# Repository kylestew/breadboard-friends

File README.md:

breadboard-friends
==================

https://mutable-instruments.net/archive/bbf/

A collection of cute breakout boards riding solderless breadboards, mostly for analog audio works

These PCB layouts and schematics are released under a Creative Commons cc-by-sa
3.0 license.

## On Oshpark

[Pots](https://oshpark.com/shared_projects/UcXFKgxV)
[Jacks](https://oshpark.com/shared_projects/G3ySjTBK)

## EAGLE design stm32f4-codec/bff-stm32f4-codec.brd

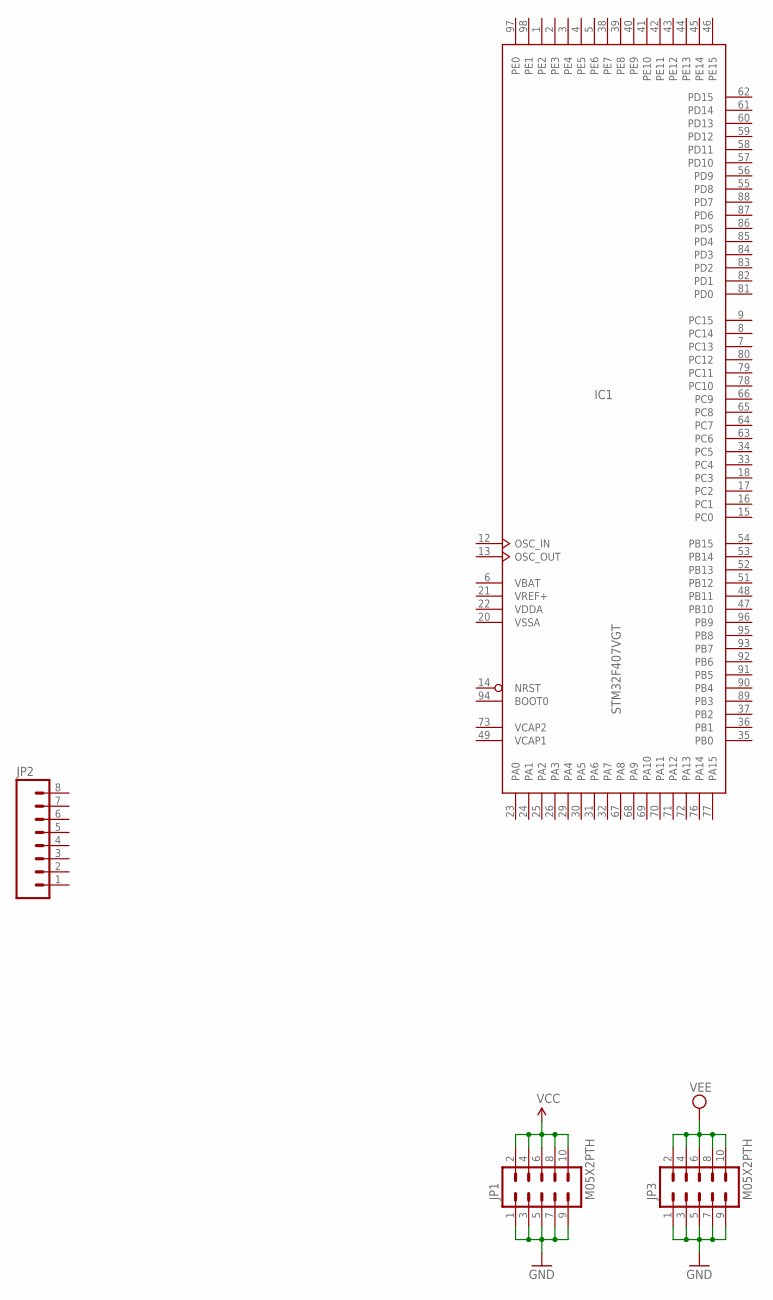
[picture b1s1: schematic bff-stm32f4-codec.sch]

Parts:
IC1: STM32F407VGT; LQFP100
JP1, JP3: M05X2PTH; AVR_ICSP
JP2: M08; 1X08

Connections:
GND: JP1.1, JP1.3, JP1.5, JP1.7, JP1.9, JP3.1, JP3.3, JP3.5, JP3.7, JP3.9
VBAT: IC1.6 (VBAT)
VCAP1: IC1.49 (VCAP1)
VCAP2: IC1.73 (VCAP2)
VCC: JP1.2, JP1.4, JP1.6, JP1.8, JP1.10
VDD: IC1.11 (VDD), IC1.19 (VDD), IC1.28 (VDD), IC1.50 (VDD), IC1.75 (VDD), IC1.100 (VDD)
VDDA: IC1.22 (VDDA)
VEE: JP3.2, JP3.4, JP3.6, JP3.8, JP3.10
VREF+: IC1.21 (VREF+)
VSS: IC1.10 (VSS), IC1.27 (VSS), IC1.74 (VSS), IC1.99 (VSS)
VSSA: IC1.20 (VSSA)

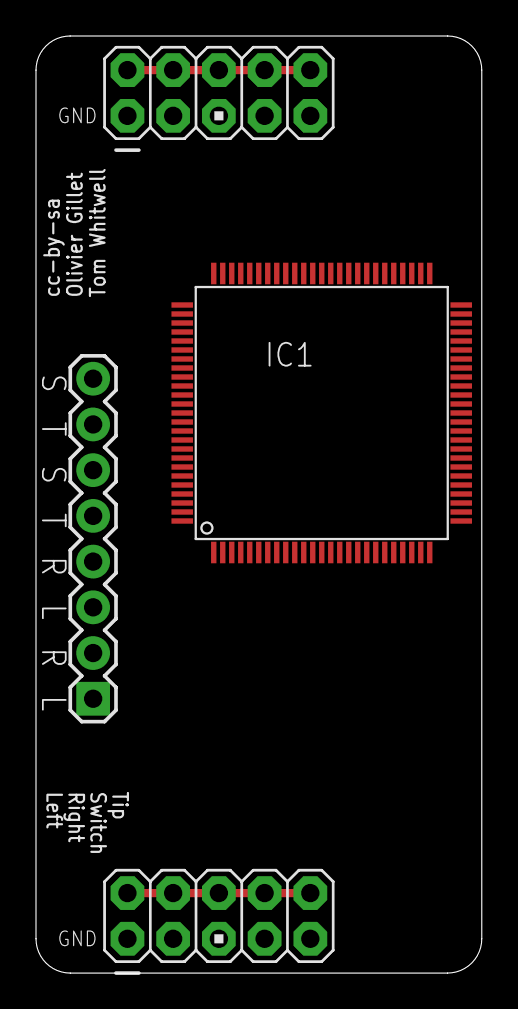
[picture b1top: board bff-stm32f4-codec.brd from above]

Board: 2 copper layers, 24.8 x 52.1 mm, 4 parts (0 on the bottom side), 5 nets.

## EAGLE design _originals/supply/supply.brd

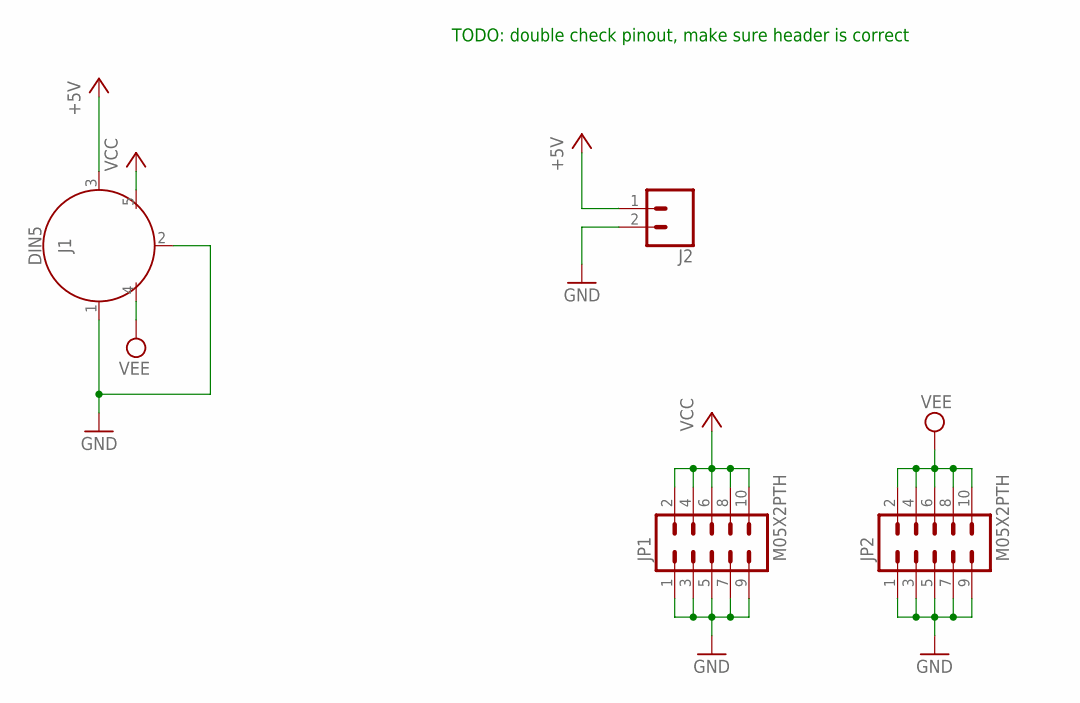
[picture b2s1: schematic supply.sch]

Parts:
J1: DIN5; DIN5-RA-PTH
J2: CONN_02; 1X02
JP1, JP2: M05X2PTH; AVR_ICSP

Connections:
+5V: J1.3, J2.1
GND: J1.1, J1.2, J2.2, JP1.1, JP1.3, JP1.5, JP1.7, JP1.9, JP2.1, JP2.3, JP2.5, JP2.7, JP2.9
VCC: J1.5, JP1.2, JP1.4, JP1.6, JP1.8, JP1.10
VEE: J1.4, JP2.2, JP2.4, JP2.6, JP2.8, JP2.10

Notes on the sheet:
TODO: double check pinout, make sure header is correct

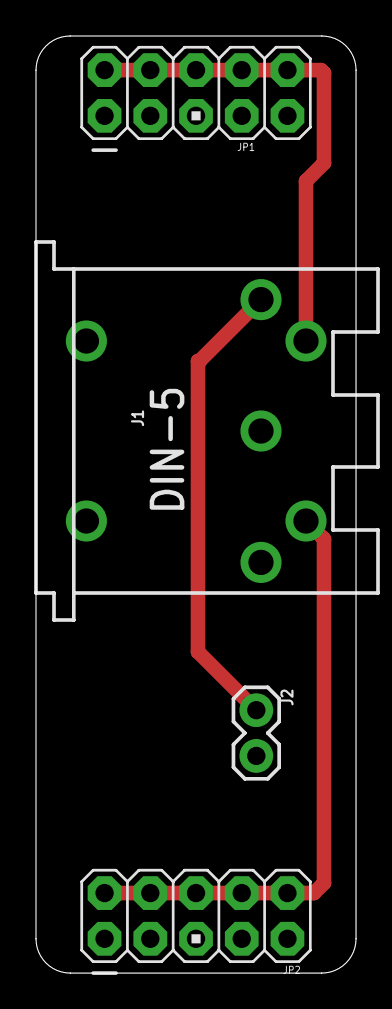
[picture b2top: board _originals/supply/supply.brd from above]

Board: 2 copper layers, 17.8 x 52.1 mm, 4 parts (0 on the bottom side), 4 nets.

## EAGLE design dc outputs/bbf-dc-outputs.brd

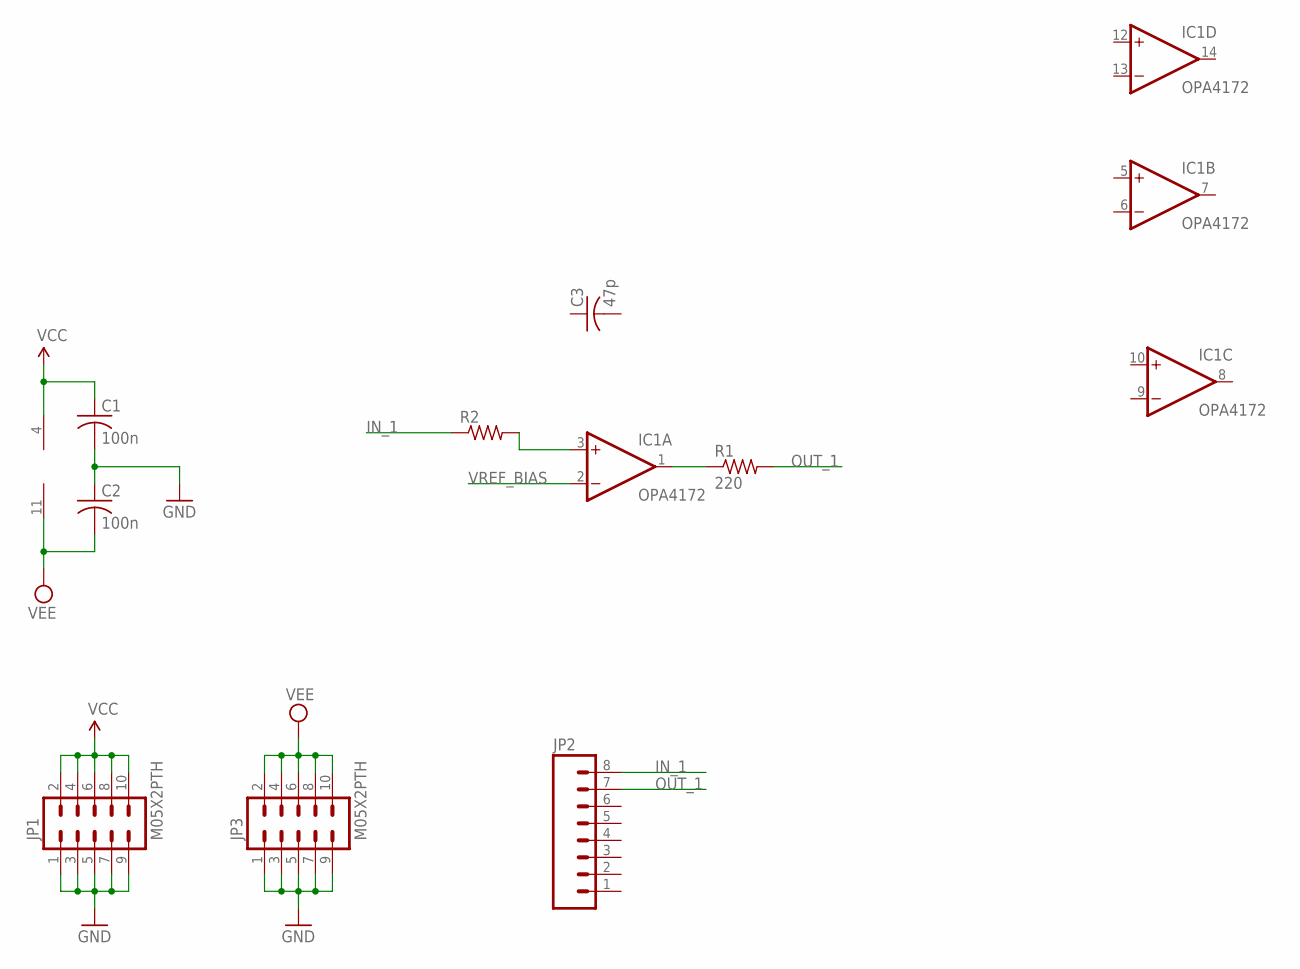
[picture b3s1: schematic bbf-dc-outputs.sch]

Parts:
C1, C2: 100n; C0805
C3: 47p; C0805
IC1: OPA4172; SO14
JP1, JP3: M05X2PTH; AVR_ICSP
JP2: M08; 1X08
R1: 220; R0805
R2: R-US_R0805; R0805

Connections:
GND: C1.2, C2.1, JP1.1, JP1.3, JP1.5, JP1.7, JP1.9, JP3.1, JP3.3, JP3.5, JP3.7, JP3.9
IN_1: JP2.8, R2.1
unnamed: IC1.1 (OUT), R1.1
unnamed: IC1.3 (+IN), R2.2
OUT_1: JP2.7, R1.2
VCC: C1.1, IC1.4 (V+), JP1.2, JP1.4, JP1.6, JP1.8, JP1.10
VEE: C2.2, IC1.11 (V-), JP3.2, JP3.4, JP3.6, JP3.8, JP3.10
VREF_BIAS: IC1.2 (-IN)

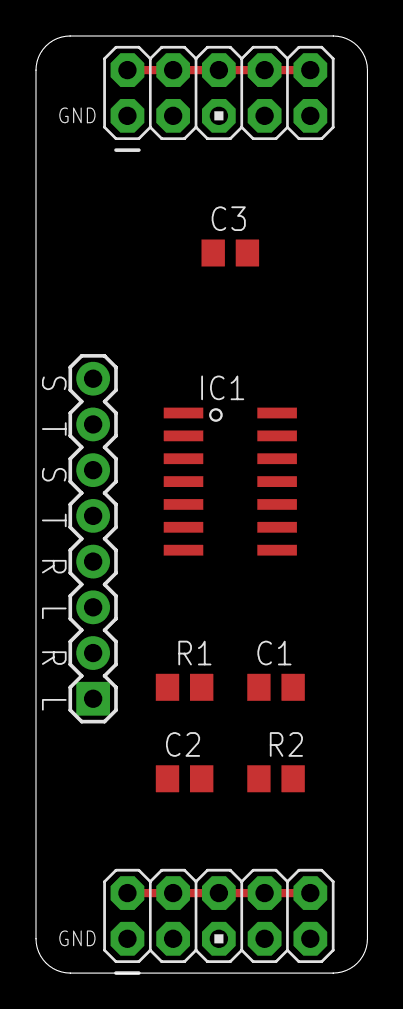
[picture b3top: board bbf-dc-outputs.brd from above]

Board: 2 copper layers, 18.4 x 52.1 mm, 9 parts (0 on the bottom side), 7 nets.

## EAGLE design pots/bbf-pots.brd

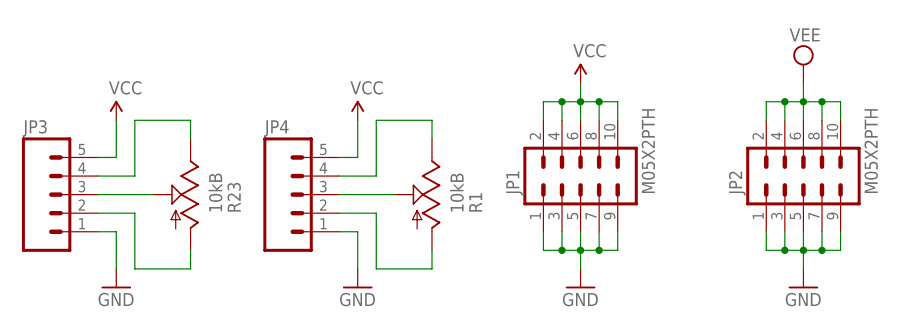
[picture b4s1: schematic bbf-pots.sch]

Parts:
JP1, JP2: M05X2PTH; AVR_ICSP
JP3, JP4: M05PTH; 1X05
R1, R23: 10kB; ALPS_POT_VERTICAL

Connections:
GND: JP1.1, JP1.3, JP1.5, JP1.7, JP1.9, JP2.1, JP2.3, JP2.5, JP2.7, JP2.9, JP3.1, JP4.1
unnamed: JP3.4, R23.P$1 (E)
unnamed: JP3.3, R23.P$2 (S)
unnamed: JP3.2, R23.P$3 (A)
unnamed: JP4.4, R1.P$1 (E)
unnamed: JP4.3, R1.P$2 (S)
unnamed: JP4.2, R1.P$3 (A)
VCC: JP1.2, JP1.4, JP1.6, JP1.8, JP1.10, JP3.5, JP4.5
VEE: JP2.2, JP2.4, JP2.6, JP2.8, JP2.10

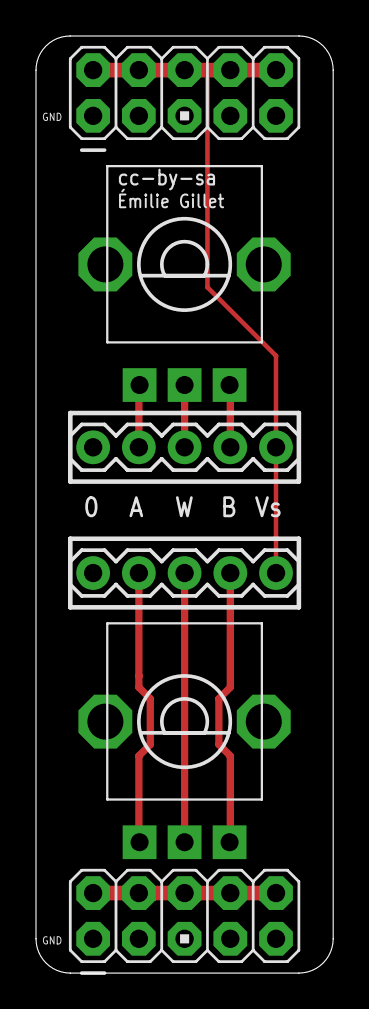
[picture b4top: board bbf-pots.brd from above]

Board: 2 copper layers, 16.5 x 52.1 mm, 6 parts (0 on the bottom side), 9 nets.

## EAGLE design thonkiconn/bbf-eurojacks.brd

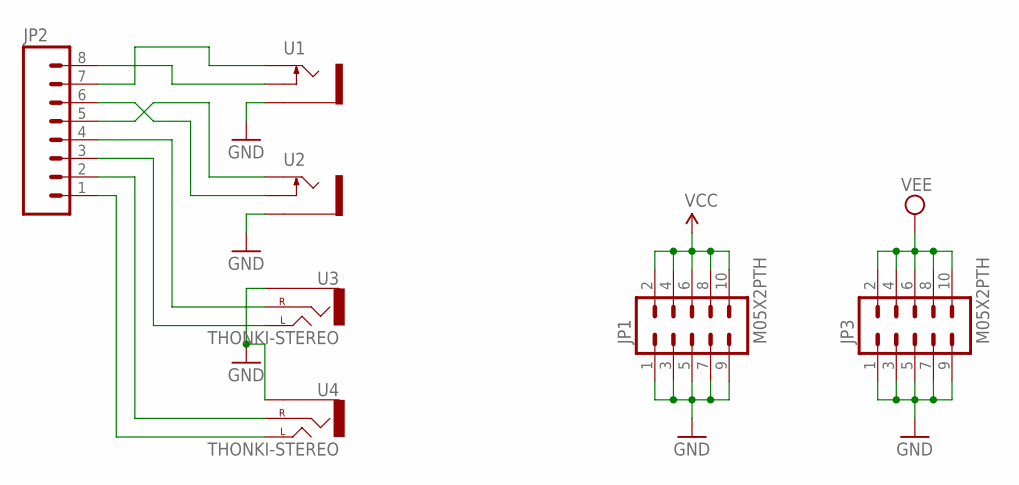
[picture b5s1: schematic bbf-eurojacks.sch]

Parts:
JP1, JP3: M05X2PTH; AVR_ICSP
JP2: M08; 1X08
U1, U2: THONKICONNNEW; WQP-PJ301M-12_JACK
U3, U4: THONKI-STEREO; WQP-PJ366ST_JACK

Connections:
2-SWITCH: JP2.6, U2.P$2_SWITCH (SWITCH)
2-TIP: JP2.5, U2.P$1_TIP (TIP)
3-LEFT: JP2.3, U3.P$1_TIP (LEFT)
3-RIGHT: JP2.4, U3.P$2_SWITCH (RIGHT)
4-LEFT: JP2.1, U4.P$1_TIP (LEFT)
4-RIGHT: JP2.2, U4.P$2_SWITCH (RIGHT)
GND: JP1.1, JP1.3, JP1.5, JP1.7, JP1.9, JP3.1, JP3.3, JP3.5, JP3.7, JP3.9, U1.P$3_SLEEVE (SLEEVE), U2.P$3_SLEEVE (SLEEVE), U3.P$3_SLEEVE (SLEEVE), U4.P$3_SLEEVE (SLEEVE)
unnamed: JP2.8, U1.P$2_SWITCH (SWITCH)
unnamed: JP2.7, U1.P$1_TIP (TIP)
VCC: JP1.2, JP1.4, JP1.6, JP1.8, JP1.10
VEE: JP3.2, JP3.4, JP3.6, JP3.8, JP3.10

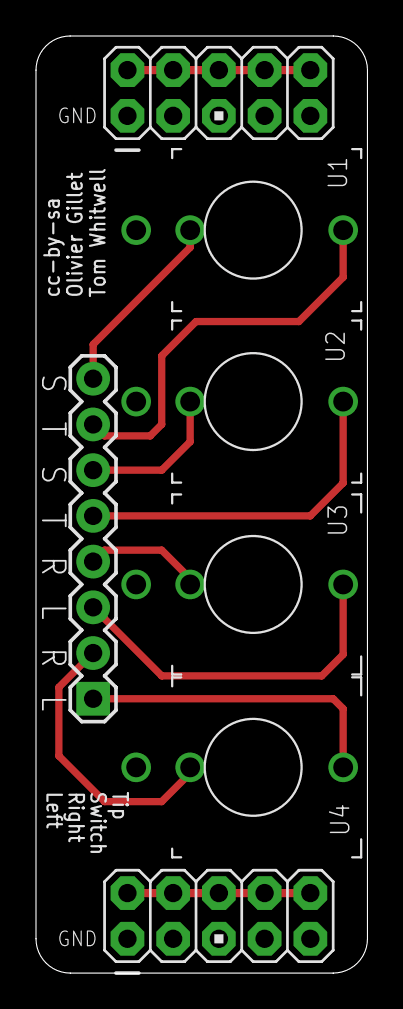
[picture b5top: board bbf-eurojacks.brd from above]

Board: 2 copper layers, 18.4 x 52.1 mm, 7 parts (0 on the bottom side), 11 nets.

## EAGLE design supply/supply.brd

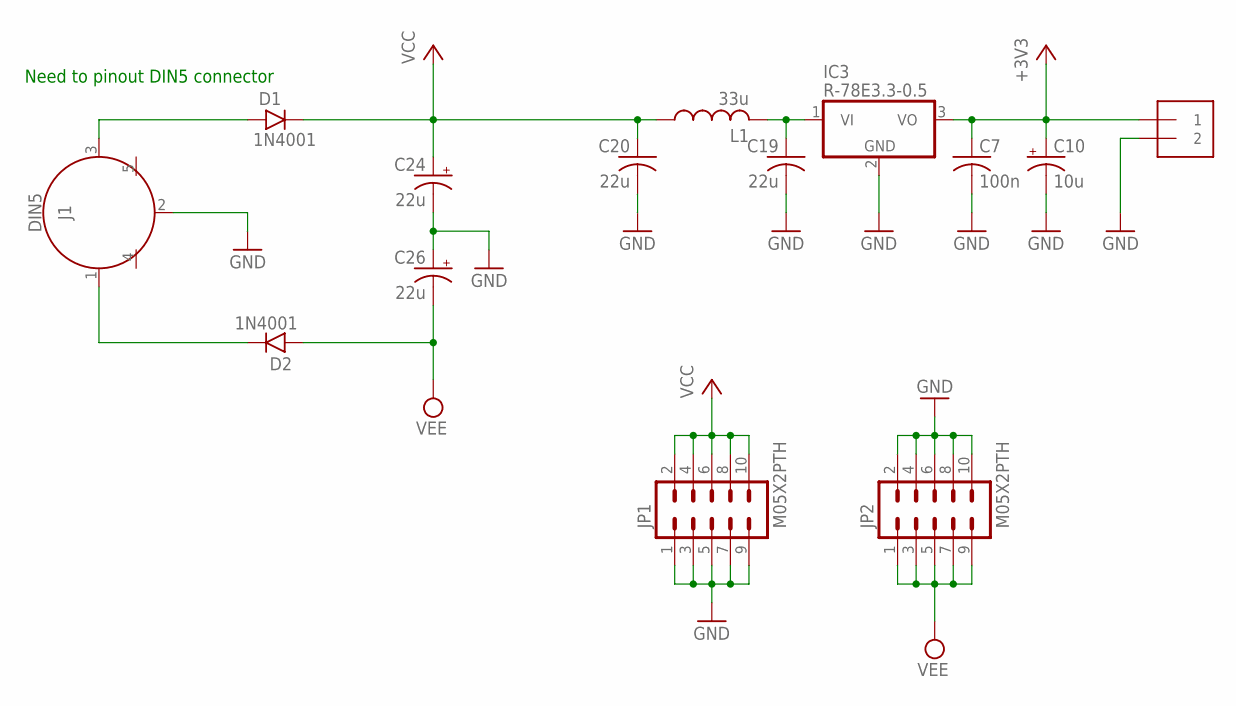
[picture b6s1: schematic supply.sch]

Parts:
C7: 100n; C0402
C10: 10u; PANASONIC_A
C19, C20: 22u; C1206
C24, C26: 22u; PANASONIC_B
D1, D2: 1N4001; DO41-3
IC3: R-78E3.3-0.5; WE78
J1: DIN5; DIN5-RA-PTH
J2: 1X2-3.5MM
JP1, JP2: M05X2PTH; AVR_ICSP
L1: 33u; L2012C

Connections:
+3V3: C7.1, C10.+, IC3.3 (VO), J2.1
GND: C7.2, C10.-, C19.2, C20.2, C24.-, C26.+, IC3.2 (GND), J1.2, J2.2, JP1.1, JP1.3, JP1.5, JP1.7, JP1.9, JP2.2, JP2.4, JP2.6, JP2.8, JP2.10
unnamed: C19.1, IC3.1 (VI), L1.2
unnamed: D1.A, J1.3
unnamed: D2.C, J1.1
VCC: C20.1, C24.+, D1.C, JP1.2, JP1.4, JP1.6, JP1.8, JP1.10, L1.1
VEE: C26.-, D2.A, JP2.1, JP2.3, JP2.5, JP2.7, JP2.9

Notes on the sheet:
Need to pinout DIN5 connector

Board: 2 copper layers, 14 parts (0 on the bottom side), 7 nets, no tracks yet.

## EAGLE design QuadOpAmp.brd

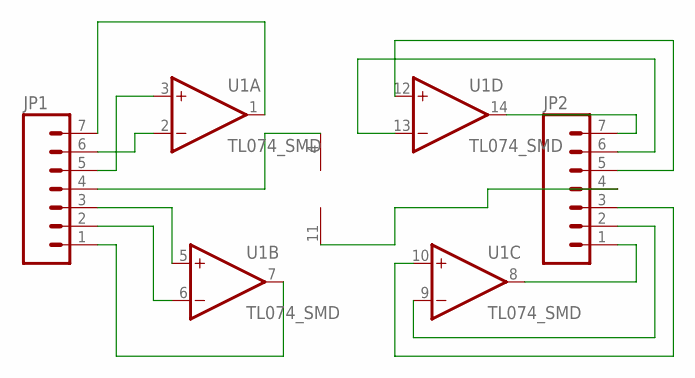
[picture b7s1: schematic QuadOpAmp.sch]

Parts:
JP1, JP2: M07LOCK; 1X07_LOCK
U1: TL074_SMD; SO14

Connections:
unnamed: JP1.1, U1.7 (OUT)
unnamed: JP1.2, U1.6 (-IN)
unnamed: JP1.3, U1.5 (+IN)
unnamed: JP1.7, U1.1 (OUT)
unnamed: JP1.6, U1.2 (-IN)
unnamed: JP1.5, U1.3 (+IN)
unnamed: JP2.1, U1.8 (OUT)
unnamed: JP2.2, U1.9 (-IN)
unnamed: JP2.3, U1.10 (+IN)
unnamed: JP2.7, U1.14 (OUT)
unnamed: JP2.6, U1.13 (-IN)
unnamed: JP2.5, U1.12 (+IN)
PWR+: JP1.4, U1.4 (V+)
PWR-: JP2.4, U1.11 (V-)

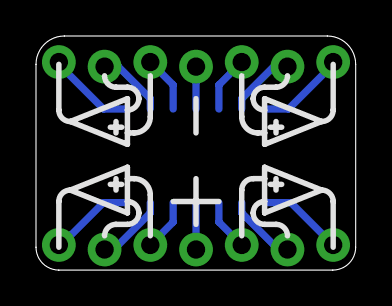
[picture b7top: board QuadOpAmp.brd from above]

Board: 2 copper layers, 17.8 x 13.0 mm, 3 parts (1 on the bottom side), 14 nets.

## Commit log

2019-06-12 Music Thing quad op amp bb friend
2019-06-12 Creating custom PSU breakout for power brick
2019-06-12 Eagle gitignore
2019-06-12 Eurojack (thonkiconn) board from Tom Whitwell
2019-06-12 Finished updated eurojacks board
2019-06-12 Updated version of pots with GND flipped
2019-06-12 Remove versions I've replaced
2019-06-12 Redo supply to be much simpler
2019-07-12 Adding more things

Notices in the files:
parts and their libraries:
SparkFun-Connectors: Licensing: CC v3.0 Share-Alike You are welcome to use this library for commercial purposes.
SparkFun-Connectors: Licensing: Creative Commons ShareAlike 4.0 International - https://creativecommons.org/licenses/by-sa/4.0
